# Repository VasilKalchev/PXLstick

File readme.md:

# <p align="center">PXL stick v1.1</p>

<p align="center">
  Board for driving WS281x lights with ESP32 running <a href="https://github.com/wled/WLED">WLED</a> firmware
</p>

![images of the 3D render of the board from different angles and of the PCB project][head_img]

-indigo?style=for-the-badge&label=fabrication%20result)
> [Release v1.1](/doc/releaselog.md#v11---2025-02-11) is a fix for v1.0, but was not fabricated at the time of release.
>
> :memo: Check the latest [release note of this version](https://github.com/VasilKalchev/PXLstick/releases/tag/v1.1) for a possible update on the fabrication status.

### WLED firmware
> [!NOTE]
> If you haven't heard of [WLED][wled_repo], it's best to check it out first.

---

## Characteristics
*The board is intended for mounting on some kind of vertical stick, that has a **WS281x LED strip** on it.*

 - Runs a **custom build** of WLED on a [ESP32-WROOM-32E][esp32_wroom_32e] module.
 - Physically controllable through **3 user configurable touch buttons** (the provided v1.1 firmware enables 2 of them: "square" and "triangle") and a **rotary encoder** for brightness and color.
 - It also has an **infrared receiver** for further flexibility.
 - Equipped with an I<sup>2</sup>S mic to enable WLED's **audio reactive** effects.
 - **Level shifted** WS281x data signal.
 - **Narrow** form factor: 25x100mm

## How to use it?

1. [PCB fabrication](#1-pcb-fabrication)
2. [Assembly](#2-assembly)
3. [Wiring and mounting](#3-wiring-and-mounting)
4. [Firmware binary](#4-firmware-binary)
5. [Flashing](#5-flashing)
6. [Configuration](#6-configuration)

### 1. PCB fabrication
The [release][repo_release_v1_1] includes [Gerber and drill files][dw_gerbers], generated according to [JLCPCB's instructions][jlcpcb_gerbers_spec]. Other fabricators may have different Gerber and drill files requirements, in which case you'll have to generate the files manually, according to their specification.

If you have made modifications to the PCB and want to regenerate the exports - you can use the scripts provided in [/hw/export/](/hw/export/).

### 2. Assembly
#### INMP441 mic
![INMP441 variants][inmp441_variants_img]

There are two footprints for the INMP441 mic. *U3* is for its 9-terminal LGA_CAV package (located on the back of the PCB) and *A1* is for its breakout board (can be soldered on either side). When using the breakout board - don't solder *C7*, *R9* and *R10*.

#### Optional peripherals
 - IR receiver (*U2, R8, C6*)
 - rotary encoder (*RE1, R2, R3, R4, C3, C4, C5*)
 - microphone (*U3/A1, R9, R10, C7*)
 - power status LED (*D1, R1*)

### 3. Wiring and mounting
The board is powered with 5V by soldering wires to the through-hole pads marked with "5V" and the symbol for ground (located below ESP32-WROOM-32E).

WS281x's data wire is soldered to the through-hole pad marked with the LED graphic.

Recommended rotary encoder's knob diameter is 20mm.

Holes *H1* and *H2* are used for mounting the board with 2mm screws.

### 4. Firmware binary
The [release][repo_release_v1_1] includes a [custom WLED build][dw_binary] compiled with a rotary encoder "usermod" and preconfigured. If you're not planning on using the rotary encoder, you can use the official build.

If you want to customize your build further - you can use my [fork of WLED][wled_fork] which includes the [configuration][wled_fork_cfg] for the custom build.

### 5. Flashing
Flashing the firmware for the first time requires connecting to the board through a USB to serial adapter.

The programming pins are exposed on the left side of the board. You can avoid soldering a pin header and just put a header or jumper wires through the plated holes.

> [!TIP]
> If you get an error while flashing firmware - try putting ESP32 in bootloader mode manually.
>
> This is done by momentarily pulling pin "EN" low (restart) while pin "BOOT" is pulled low. Pins "EN" and "BOOT" are exposed as pads, "EN" is located to the left of the ESP32 module and "BOOT" is to the right. Shorting these pads - pulls the pins low.

#### Method A: Flashing directly with Espressif's `esptool`
1. Follow the [instructions to install esptool][esptool_install].
2. Flash [WLED's bootloader][dw_bootloader]:
```
esptool.py write_flash 0x0 ./esp32_bootloader_v4.bin
```
3. Flash the firmware binary:
```
esptool.py write_flash 0x10000 ./WLED_XXX.bin
```

If you experience issues - try erasing the flash first:
```
esptool.py erase_flash
```

> [!NOTE]
> This method is taken from [WLED's documentation][wled_flash_method2] web site.

#### Method B: Flashing with WLED's web installer and performing an OTA update
You can avoid installing `esptool` by using [WLED's web installer][wled_web_installer] to flash WLED's official firmware and then performing an OTA update with the provided custom binary.

### 6. Configuration
You can now continue with [WLED's getting started guide][wled_getting_started_guide] to configure your board.

> [!TIP]
> After connecting the board to your Wi-Fi network you can apply the provided base configuration by going to "Config" > "Security & Updates" > "Restore configuration" and uploading the provided [base configuration file][dw_base_cfg] (after that, you'll have to configure the Wi-Fi again).

#### Board connections:
| Function    | GPIO    |
|-------------|---------|
| WS281x      | GPIO 4  |
| "square"    | GPIO 32 |
| "triangle"  | GPIO 33 |
| "circle"    | GPIO 14 |
| RE 1        | GPIO 27 |
| RE 2        | GPIO 16 |
| RE BTN      | GPIO 17 |
| LED         | GPIO 2  |
| IR receiver | GPIO 23 |
| INMP441 SD  | GPIO 15 |
| INMP441 WS  | GPIO 13 |
| INMP441 SCK | GPIO 25 |

<!-- links -->
[head_img]: /doc/assets/head.png
[inmp441_variants_img]: /doc/assets/inmp441_variants.png

[releaselog_v1_1]: /doc/releaselog.md#v11---2025-02-11 "/doc/releaselog.md"
[repo_release_v1_1]: https://github.com/VasilKalchev/PXLstick/releases/tag/v1.1 "PXL stick version v1.1"
[repo_releases]: https://github.com/VasilKalchev/PXLstick/releases "All PXL stick releases"

[wled_repo]: https://github.com/wled/WLED "WLED's repository"
[esp32_wroom_32e]: https://www.espressif.com/sites/default/files/documentation/esp32-wroom-32e_esp32-wroom-32ue_datasheet_en.pdf "ESP32-WROOM-32E datasheet"
[inmp441]: https://invensense.tdk.com/wp-content/uploads/2015/02/INMP441.pdf "INMP441 datasheet"
[jlcpcb_gerbers_spec]: https://jlcpcb.com/help/article/362-how-to-generate-gerber-and-drill-files-in-kicad-7 "JLCPCB: How to generate Gerber and drill files in KiCad 7"

[dw_gerbers]: https://github.com/VasilKalchev/PXLstick/releases/download/v1.1/gerbers_jlcpcb.zip "Download gerbers_jlcpcb.zip"
[dw_binary]: https://github.com/VasilKalchev/PXLstick/releases/download/v1.1/WLED_0.14.3_PXLstick_v1.1.bin "Download WLED_0.14.3_PXLstick_v1.1.bin"
[dw_bootloader]: https://github.com/wled/WLED/releases/download/v0.13.1/esp32_bootloader_v4.bin "Download esp32_bootloader_v4.bin"
[dw_base_cfg]: https://github.com/VasilKalchev/PXLstick/releases/download/v1.1/WLED_0.14.3_PXLstick_v1.1_basecfg.json "Download WLED_0.14.3_PXLstick_v1.1_basecfg.json"

[wled_fork]: https://github.com/VasilKalchev/WLED "Fork of WLED repository for custom builds"
[wled_fork_cfg]: https://github.com/VasilKalchev/WLED/blob/4febf0a671bf4d266bcb785312891e56a2469468/platformio.ini#L836-L875 "Custom build configuration for PXL stick v1"

[esptool_install]: https://docs.espressif.com/projects/esptool/en/latest/esp32/ "Espressif's esptool.py documentation"
[wled_web_installer]: https://install.wled.me/

[wled_flash_method2]: https://kno.wled.ge/basics/install-binary/#:~:text=properly%20by%20WLED.-,Flashing%20method%202%3A%20esptool,-First%20of%20all "WLED's flashing guide: method 2"
[wled_getting_started_guide]: https://kno.wled.ge/basics/getting-started/#:~:text=3.%20Use%20a%20WiFi%20device%20to%20connect%20to%20the%20access%20point%20WLED%2DAP "WLED's getting started guide: Wi-Fi configuration"

<!-- checklist & fabrication result template

<details>
<summary>/readme.md checklist</summary>

 - [x] set current version (after project name)
 - [x] set fabrication status
 - [x] update sections: [Characteristics](#characteristics) and [How to use it?](#how-to-use-it)
 - [x] comment out this "checklist" and "templates" sections

</details>

<details>
<summary>/readme.md templates</summary>

## "Fabrication result" section:

> The fabricated board from release vX.Y [didn't work](/doc/releaselog.md#vXY---202Y-MM-DD).
>
> :exclamation: Browse [repository releases][repo_releases] for a better version.

---

> The fabricated board from release vX.Y worked, but has [significant problems](/doc/releaselog.md#vXY---202Y-MM-DD).
>
> :exclamation: Browse [repository releases][repo_releases] for a better version.

---

> The fabricated board from release vX.Y worked, but has [some problems](/doc/releaselog.md#vXY---202Y-MM-DD).
>
> :grey_exclamation: Browse [repository releases][repo_releases] for a better version.

---

> The fabricated board from release vX.Y worked, but has [minor problems](/doc/releaselog.md#vXY---202Y-MM-DD).
>
> :memo: Browse [repository releases][repo_releases] for a better version.

---

> The fabricated board from release vX.Y worked without problems!
>
> :tada: Recommended for fabrication.

---

> This version is currently in development...
>
> :hourglass_flowing_sand: Wait for the release or browse [repository releases][repo_releases] for an older, completed version.

---

> Release vX.Y won't be fabricated, because ... .
>
> :exclamation: Browse [repository releases][repo_releases] for a better version.

---

-indigo?style=for-the-badge&label=fabrication%20result)
> [Release vX.Y](/doc/releaselog.md#vXY---202Y-MM-DD) is a fix for vX.Y, but was not fabricated at the time of release.
>
> :memo: Check the latest [release note of this version](https://github.com/VasilKalchev/PXLstick/releases/tag/vX.Y) for a possible update on the fabrication status.

</details>

-->

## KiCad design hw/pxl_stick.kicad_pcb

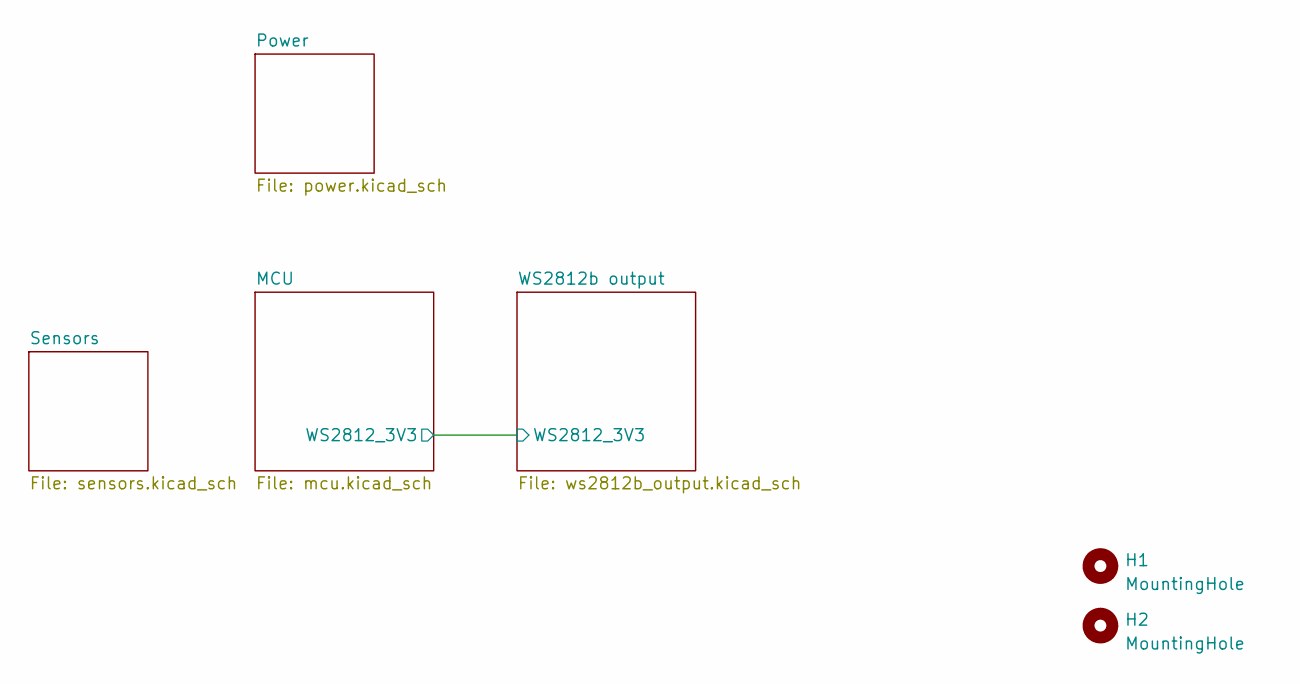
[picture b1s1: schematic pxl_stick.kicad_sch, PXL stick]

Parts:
H1, H2: MountingHole; MountingHole_2.2mm_M2_ISO14580_Pad_TopOnly

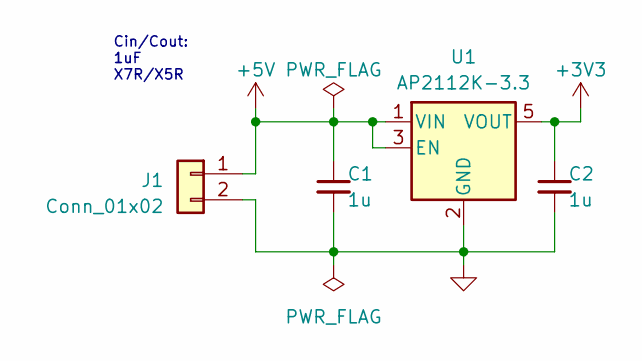
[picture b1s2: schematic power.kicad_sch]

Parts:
C1, C2: 1u; C_0805_2012Metric_Pad1.18x1.45mm_HandSolder
J1: Conn_01x02; SolderWire-0.5sqmm_1x02_P4.6mm_D0.9mm_OD2.1mm
U1: AP2112K-3.3; SOT-23-5_HandSoldering

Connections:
+3V3: C2.1, U1.5 (VOUT); also elsewhere on the board
+5V: C1.1, J1.1, U1.1 (VIN), U1.3 (EN); also elsewhere on the board
GND: C1.2, C2.2, J1.2, U1.2 (GND); also elsewhere on the board

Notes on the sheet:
Cin/Cout: 1uF X7R/X5R

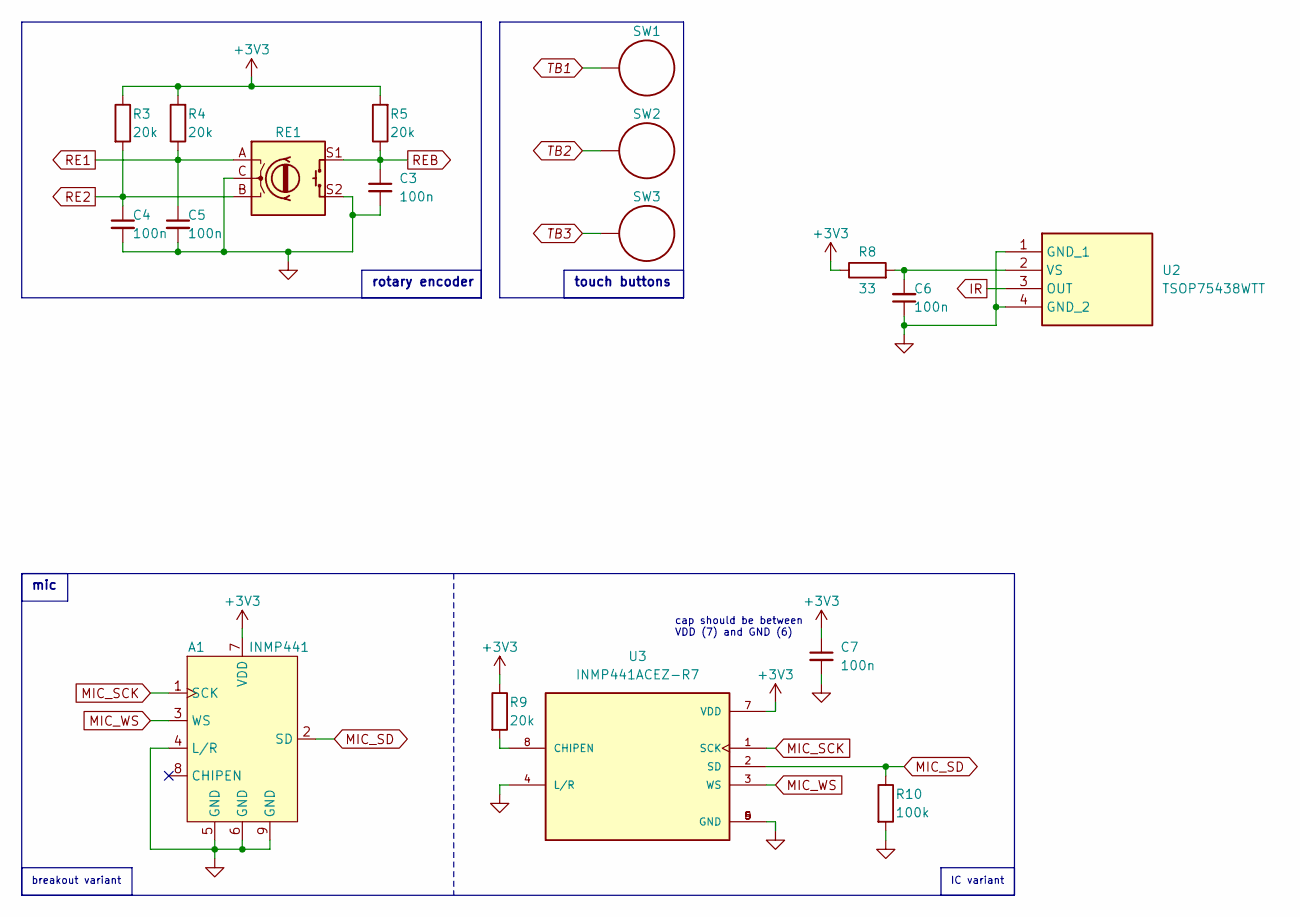
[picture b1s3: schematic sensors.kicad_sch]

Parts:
A1: INMP441; INMP441 breakout
C3, C4, C5, C6, C7: 100n; C_0805_2012Metric_Pad1.18x1.45mm_HandSolder
R3, R4, R5, R9: 20k; R_0805_2012Metric_Pad1.20x1.40mm_HandSolder
R8: 33; R_0805_2012Metric_Pad1.20x1.40mm_HandSolder
R10: 100k; R_0805_2012Metric_Pad1.20x1.40mm_HandSolder
RE1: RotaryEncoder_Switch; RotaryEncoder_Alps_EC11E-Switch_Vertical_H20mm
SW1, SW2, SW3: Touch_Circular_10mm
U2: TSOP75438WTT; TSOP75_WTT_VIS; Mouser Part Number 78-TSOP75438WTT
U3: INMP441ACEZ-R7; PARTREV 1.1

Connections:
+3V3: A1.7 (VDD), C7.1, R3.1, R4.2, R5.2, R8.1, R9.1, U3.7 (VDD); also elsewhere on the board
GND: A1.4 (L/R), A1.5 (GND), A1.6 (GND), A1.9 (GND), C3.2, C4.2, C5.2, C6.1, C7.2, R10.2, RE1.C, RE1.S2, U2.1 (GND_1), U2.4 (GND_2), U3.4 (L/R), U3.5 (GND), U3.6 (GND), U3.9 (GND); also elsewhere on the board
IR: U2.3 (OUT); also elsewhere on the board
MIC_SCK: A1.1 (SCK), U3.1 (SCK); also elsewhere on the board
MIC_SD: A1.2 (SD), R10.1, U3.2 (SD); also elsewhere on the board
MIC_WS: A1.3 (WS), U3.3 (WS); also elsewhere on the board
unnamed: C6.2, R8.2, U2.2 (VS)
unnamed: R9.2, U3.8 (CHIPEN)
RE1: C5.1, R4.1, RE1.A; also elsewhere on the board
RE2: C4.1, R3.2, RE1.B; also elsewhere on the board
REB: C3.1, R5.1, RE1.S1; also elsewhere on the board
TB1: SW1.1; also elsewhere on the board
TB2: SW2.1; also elsewhere on the board
TB3: SW3.1; also elsewhere on the board

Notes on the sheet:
rotary encoder
touch buttons
cap should be between VDD (7) and GND (6)
mic
breakout variant
IC variant

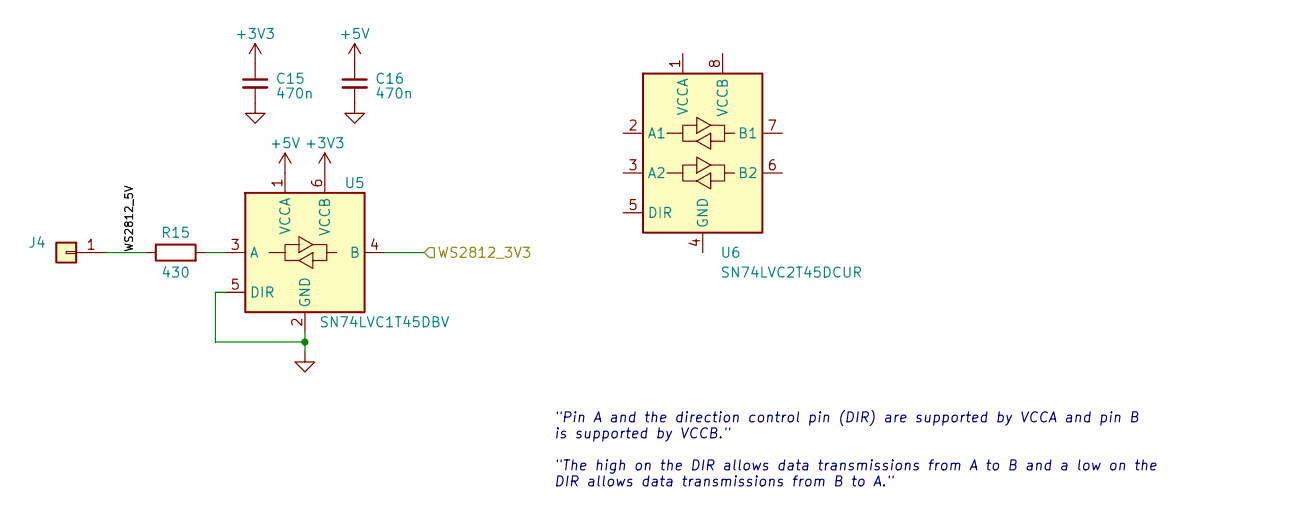
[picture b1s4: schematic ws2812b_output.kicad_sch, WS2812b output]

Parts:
C15, C16: 470n; C_0805_2012Metric_Pad1.18x1.45mm_HandSolder
J4: Conn_01x01; SolderWire-0.5sqmm_1x01_D0.9mm_OD2.1mm
R15: 430; R_0805_2012Metric_Pad1.20x1.40mm_HandSolder
U5: SN74LVC1T45DBV; SOT-23-6
U6: SN74LVC2T45DCUR; VSSOP-8_2.3x2mm_P0.5mm

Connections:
+3V3: C15.1, U5.6 (VCCB); also elsewhere on the board
+5V: C16.1, U5.1 (VCCA); also elsewhere on the board
/MCU/WS2812_3V3: U5.4 (B); also elsewhere on the board
/WS2812b output/WS2812_5V: J4.1, R15.1
GND: C15.2, C16.2, U5.2 (GND), U5.5 (DIR); also elsewhere on the board
unnamed: R15.2, U5.3 (A)

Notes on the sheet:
"Pin A and the direction control pin (DIR) are supported by VCCA and pin B is supported by VCCB." "The high on the DIR allows data transmissions from A to B and a low on the DIR allows data transmissions from B to A."

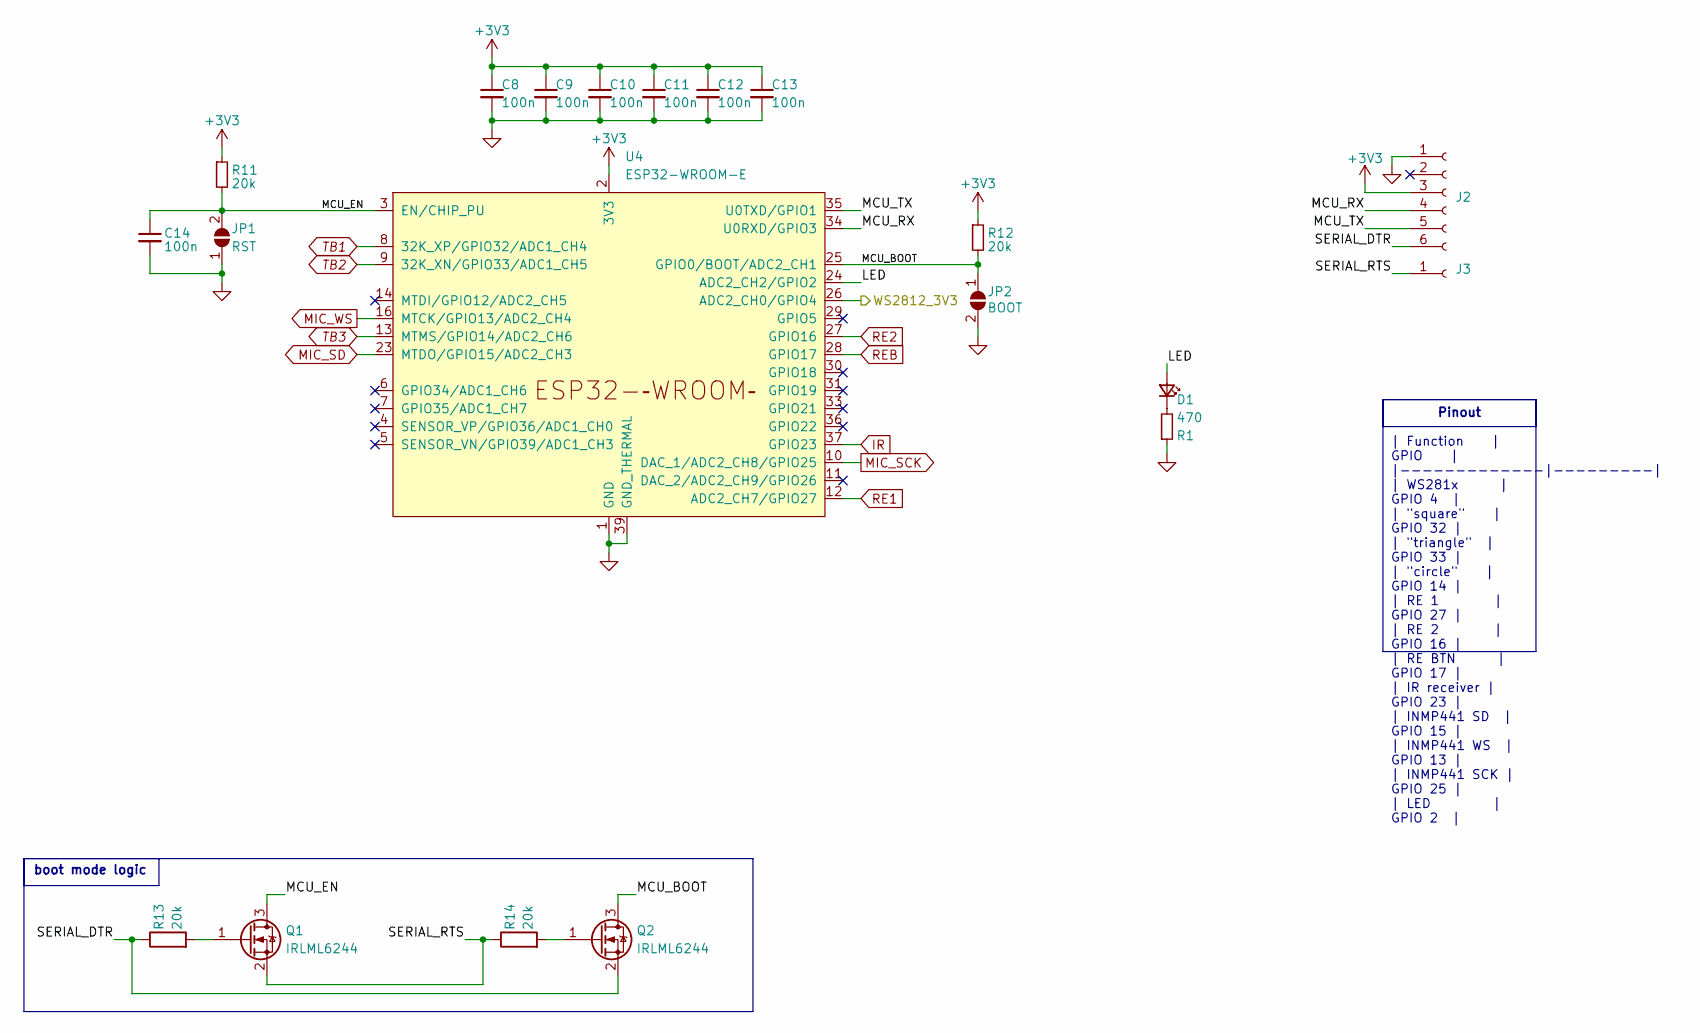
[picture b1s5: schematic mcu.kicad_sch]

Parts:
C8: 100n; C_1206_3216Metric_Pad1.33x1.80mm_HandSolder
C9, C10, C11, C12, C13, C14: 100n; C_0805_2012Metric_Pad1.18x1.45mm_HandSolder
D1: LED_Small; LED_0805_2012Metric_Pad1.15x1.40mm_HandSolder
J2: Conn_01x06_Socket; PinSocket_1x06_P2.54mm_Vertical
J3: Conn_01x01_Socket; PinSocket_1x01_P2.54mm_Vertical
JP1: RST; SolderJumper-2_P1.3mm_Open_TrianglePad1.0x1.5mm
JP2: BOOT; SolderJumper-2_P1.3mm_Open_TrianglePad1.0x1.5mm
Q1, Q2: IRLML6244; SOT-23
R1: 470; R_0805_2012Metric_Pad1.20x1.40mm_HandSolder
R11, R12, R13, R14: 20k; R_0805_2012Metric_Pad1.20x1.40mm_HandSolder
U4: ESP32-WROOM-E; ESP32-WROOM-32E

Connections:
+3V3: C8.1, C9.1, C10.1, C11.1, C12.1, C13.1, J2.3, R11.1, R12.1, U4.2 (3V3); also elsewhere on the board
/MCU/LED: D1.2 (A), U4.24 (ADC2_CH2/GPIO2)
/MCU/MCU_BOOT: JP2.1 (A), Q2.3 (D), R12.2, U4.25 (GPIO0/BOOT/ADC2_CH1)
/MCU/MCU_EN: C14.1, JP1.2 (B), Q1.3 (D), R11.2, U4.3 (EN/CHIP_PU)
/MCU/MCU_RX: J2.4, U4.34 (U0RXD/GPIO3)
/MCU/MCU_TX: J2.5, U4.35 (U0TXD/GPIO1)
/MCU/SERIAL_DTR: J2.6, Q2.2 (S), R13.1
/MCU/SERIAL_RTS: J3.1, Q1.2 (S), R14.1
/MCU/WS2812_3V3: U4.26 (ADC2_CH0/GPIO4); also elsewhere on the board
GND: C8.2, C9.2, C10.2, C11.2, C12.2, C13.2, C14.2, J2.1, JP1.1 (A), JP2.2 (B), R1.1, U4.1 (GND), U4.15 (GND), U4.38 (GND), U4.39 (GND_THERMAL); also elsewhere on the board
IR: U4.37 (GPIO23); also elsewhere on the board
MIC_SCK: U4.10 (DAC_1/ADC2_CH8/GPIO25); also elsewhere on the board
MIC_SD: U4.23 (MTDO/GPIO15/ADC2_CH3); also elsewhere on the board
MIC_WS: U4.16 (MTCK/GPIO13/ADC2_CH4); also elsewhere on the board
unnamed: D1.1 (K), R1.2
unnamed: Q1.1 (G), R13.2
unnamed: Q2.1 (G), R14.2
RE1: U4.12 (ADC2_CH7/GPIO27); also elsewhere on the board
RE2: U4.27 (GPIO16); also elsewhere on the board
REB: U4.28 (GPIO17); also elsewhere on the board
TB1: U4.8 (32K_XP/GPIO32/ADC1_CH4); also elsewhere on the board
TB2: U4.9 (32K_XN/GPIO33/ADC1_CH5); also elsewhere on the board
TB3: U4.13 (MTMS/GPIO14/ADC2_CH6); also elsewhere on the board

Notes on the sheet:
| Function | GPIO | |-------------|---------| | WS281x | GPIO 4 | | "square" | GPIO 32 | | "triangle" | GPIO 33 | | "circle" | GPIO 14 | | RE 1 | GPIO 27 | | RE 2 | GPIO 16 | | RE BTN | GPIO 17 | | IR receiver | GPIO 23 | | INMP441 SD | GPIO 15 | | INMP441 WS | GPIO 13 | | INMP441 SCK | GPIO 25 | |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
Pinout
boot mode logic

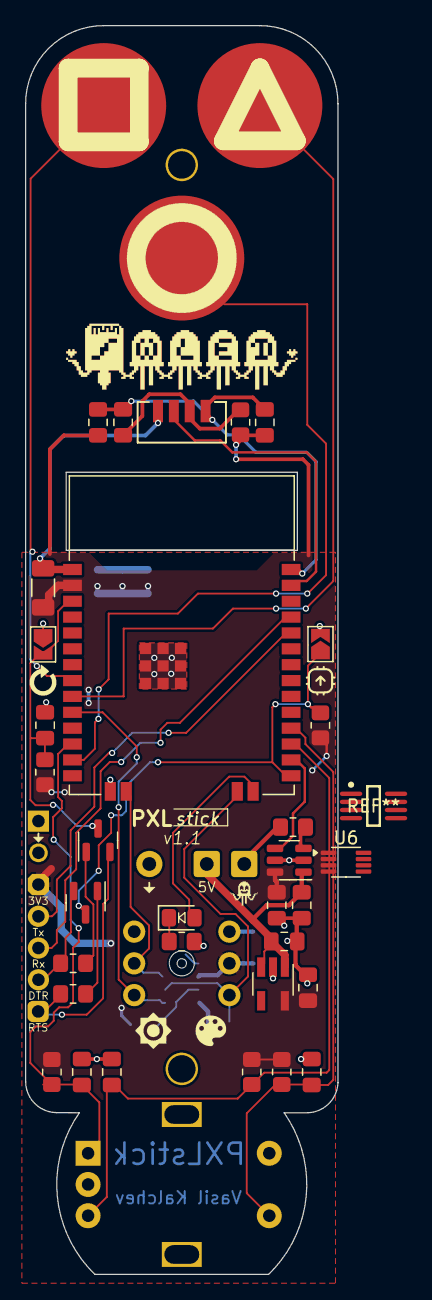
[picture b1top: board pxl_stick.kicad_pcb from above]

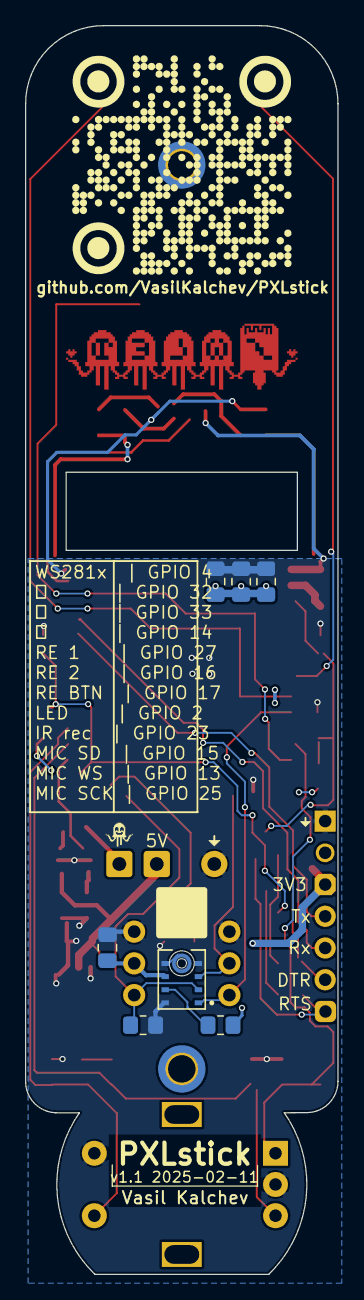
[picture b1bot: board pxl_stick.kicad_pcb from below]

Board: 2 copper layers, 25.0 x 99.9 mm, 57 parts (12 on the bottom side), 28 nets.

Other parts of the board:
ss1: qr; LOGO
ss2: wled logo; LOGO
ss3: ws281x signal; LOGO
ss4: brightness; LOGO
ss5: palette; LOGO
ss6: reset; LOGO
ss7: bootloader; LOGO

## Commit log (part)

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2024-05-07 Corrections
2024-05-08 Initialize docs for new version development
2024-05-08 Enable detection of KiCad files by linguist
2024-05-08 Enable detection of KiCad files by linguist (#1)
2025-02-11 Version 1.1 changes
2025-02-11 Export render
2025-02-11 Ignore exported 3d models and KiCad temporary files
2025-02-11 Make some paragraphs clearer
2025-02-11 Export and process new images of the board
2025-02-11 Check completed
2025-02-11 Remove expored library
2025-02-11 Change to single board
2025-02-12 Add checklists for the new release
2025-02-12 Add footprint for 2 channel level shifter
2025-02-12 Edit board constraints
2025-02-12 Fix via annular width, remove netties
2025-02-20 change smalles hole to 0.3mm
2025-02-22 Move the images to their own folder
2025-02-22 Add 3D models for rotary encoder knobs
2025-02-22 Change FR-4 color to black for better 3D image export
2025-02-22 Add fabrication properties
